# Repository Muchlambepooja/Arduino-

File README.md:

<!--Heading-->
# Arduino-Board
<!--links-->

##  Table of Contents

* [1. Introduction]()

* [2.Power Module](https://user-images.githubusercontent.com/91477166/134933617-c281e0b7-52b0-430e-a4fc-98a04329524c.PNG)

* [3. Voltage Regulator](https://user-images.githubusercontent.com/91477166/137732301-d14b79bf-847d-4a53-ac1d-5a26da9be1a0.jpg)

* [4. Power_jackpth_lock](https://user-images.githubusercontent.com/91477166/137733125-0d70d7f8-92f7-4a11-a70f-299146b748ae.png)

* [5. Capacitor](https://user-images.githubusercontent.com/91477166/137733573-614a9385-2981-4580-8750-bcf8b14b4d77.jpg)

* [6. Microcontroller](https://user-images.githubusercontent.com/91477166/134943802-9d5f9fb5-34e9-4055-a048-e4feaa09a2d5.PNG)

* [7. Schematic](https://user-images.githubusercontent.com/91477166/134953086-77eabae7-3045-4bdb-ab8c-5c033848843d.png)

* [8. Board](https://user-images.githubusercontent.com/91477166/134954367-aeb1af29-25dc-444c-b872-aa8de7bfb5b1.png)

* [9. Top Layer](https://user-images.githubusercontent.com/91477166/134954817-afc4833a-c6b3-4553-b30f-944d2f450a21.png)

* [10. Bottom Layer](https://user-images.githubusercontent.com/91477166/134955356-d5f6bea5-aa2f-4f7f-b24b-226915f9a1c8.png)

* [11. Future Scope]()

* [12. Contributors]()

<!---links-->

# Introduction :
This repository presents  the design of Arduino Board .The boards are equipped with sets of digital and analog input/output (I/O) pins that may be interfaced to various expansion boards ('shields') or breadboards (for prototyping) and other circuits. The boards feature serial communications interfaces, we need to use external  Universal Serial Bus (USB) on some models, which are also used for loading programs . 

The below figure shows the power module of arduino board using eagle tool.

# Power Module

This Power Module Consist of Voltage Regulator, Power_jackpth_lock, 2-Capacitors and vcc.with Input voltage 7V to 16V .

##  Voltage Regulator:
A voltage regulator is a system designed to automatically maintain a constant voltage. A voltage regulator may use a simple feed-forward design or may include negative feedback. It may use an electromechanical mechanism, or electronic components. Depending on the design, it may be used to regulate one or more AC or DC voltages.
Electronic voltage regulators are found in devices such as computer power supplies where they stabilize the DC voltages used by the processor and other elements. In automobile alternators and central power station generator plants, voltage regulators control the output of the plant. In an electric power distribution system, voltage regulators may be installed at a substation or along distribution lines so that all customers receive steady voltage independent of how much power is drawn from the line.

##  Power_jackpth_lock:
Power circuit wired up
Whenever a net splits in two directions a junction node is created. This signifies that all three intersecting nets are connected. If two nets cross, but there's not a junction, those nets are not connected.

##  Capacitor:
A capacitor is a device that stores electrical energy in an electric field. It is a passive electronic component with two terminals.
The effect of a capacitor is known as capacitance. While some capacitance exists between any two electrical conductors in proximity in a circuit, a capacitor is a component designed to add capacitance to a circuit. The capacitor was originally known as a condenser or condensator.This name and its cognates are still widely used in many languages, but rarely in English, one notable exception being condenser microphones, also called capacitor microphones.

##  Microcontroller:

ATmega328P is a high performance yet low power consumption 8-bit AVR microcontroller that’s able to achieve the most single clock cycle execution of 131 powerful instructions thanks to its advanced RISC architecture. It can commonly be found as a processor in Arduino boards such as Arduino Fio and Arduino Uno.

##  Features and Parametrics

### Features:
High endurance non-volatile memory segments

In system self-programmable flash program memory
Programming Lock for software security

###  Peripheral feature:

Two 8-bit Timer/Counter with separate prescaler, compare mode.
One 16-bit Timer/Counter with separate prescaler, compare mode, and capture mode

###   Temperature measurement:

Programmable serial USART and watchdog timer with separate on-chip oscillator

Unique features compared to other microcontrollers (ARM, 8051, PIC):

Power-on reset and programmable brown-out detection
Internal calibrated oscillator
External and Internal interrupt sources

Six sleep modes: Idle, ADC noise reduction, power-save, power-down, standby, and extended standby

###  Parametrics:

Program Memory Type:	Flash

Program Memory Size:	32

CPU Speed (MIPS/DMIPS) :	20

SRAM (KB)	:2,048

Data EEPROM/HEF (bytes)	1,024

Digital Communication Peripheral :	1-UART, 2-SPI, 1-I2C

Capture/Compare/PWM Peripheral :	1 Input Capture, 1 CCP, 6PWM

Number of Comparators :	1

Temperature Range	: -40 to 85deg

Operating Voltage Range (V) :	1.8 to 5.5V

Pin Count	: 28

Low Power:	Yes

###  Advantages and Disadvantages:

####  Advantages:

Processors are simpler to use, with the usage of 8bit and 16bit instead of 32/64bit which are more complex
Readily usable without additional computing components with 32k bytes of onboard self-programmable flash program memory as well as 23 programmable I/O lines
Code Efficient, all 31 registers are directly connected to the arithmetic logic unit (ALU), making it 10 times faster than conventional CISC microcontrollers
Optimized for AVR enhanced RISC instruction set.

#### Disadvantages:

Lacks performance compared to higher bit microcontrollers
Product Applications
The ATmega328P is supported with a full suite of program and system development tools which includes: C compilers, macro assemblers, program debugger/simulators, in-circuit emulators, and evaluation kits.

The fast PWM mode that provides a high-frequency PWM waveform generation allows for it to be suited for power regulation, rectification, and DAC applications.

We have also used Header Pins as shown below

# Schematic

The Arduino project began in 2005 as a tool for students at the Interaction Design Institute Ivrea, Italy, aiming to provide a low-cost and easy way for novices and professionals to create devices that interact with their environment using sensors and actuators. Common examples of such devices intended for beginner hobbyists include simple robots, thermostats and motion detectors.

##   Board:

##  Top layer:

##  Bottom Layer:

##  Future Scope:

the Arduino platform has done is to take what was once a fragmented and expensive market for robotics and microprocessors and become the major platform, largely by virtue of much lower cost and ease of use, leading to higher volume and popularity, and community support behind it. Arduino has made it simple to program their boards with any computer via USB and simple to integrate with a wide array of sensors and devices.

##  Contributors:

 Muchlambe Pooja ,B.Tech(Electronics and Communication Engineering), Jawaharlal Nehru Technological University, Hyderabad.

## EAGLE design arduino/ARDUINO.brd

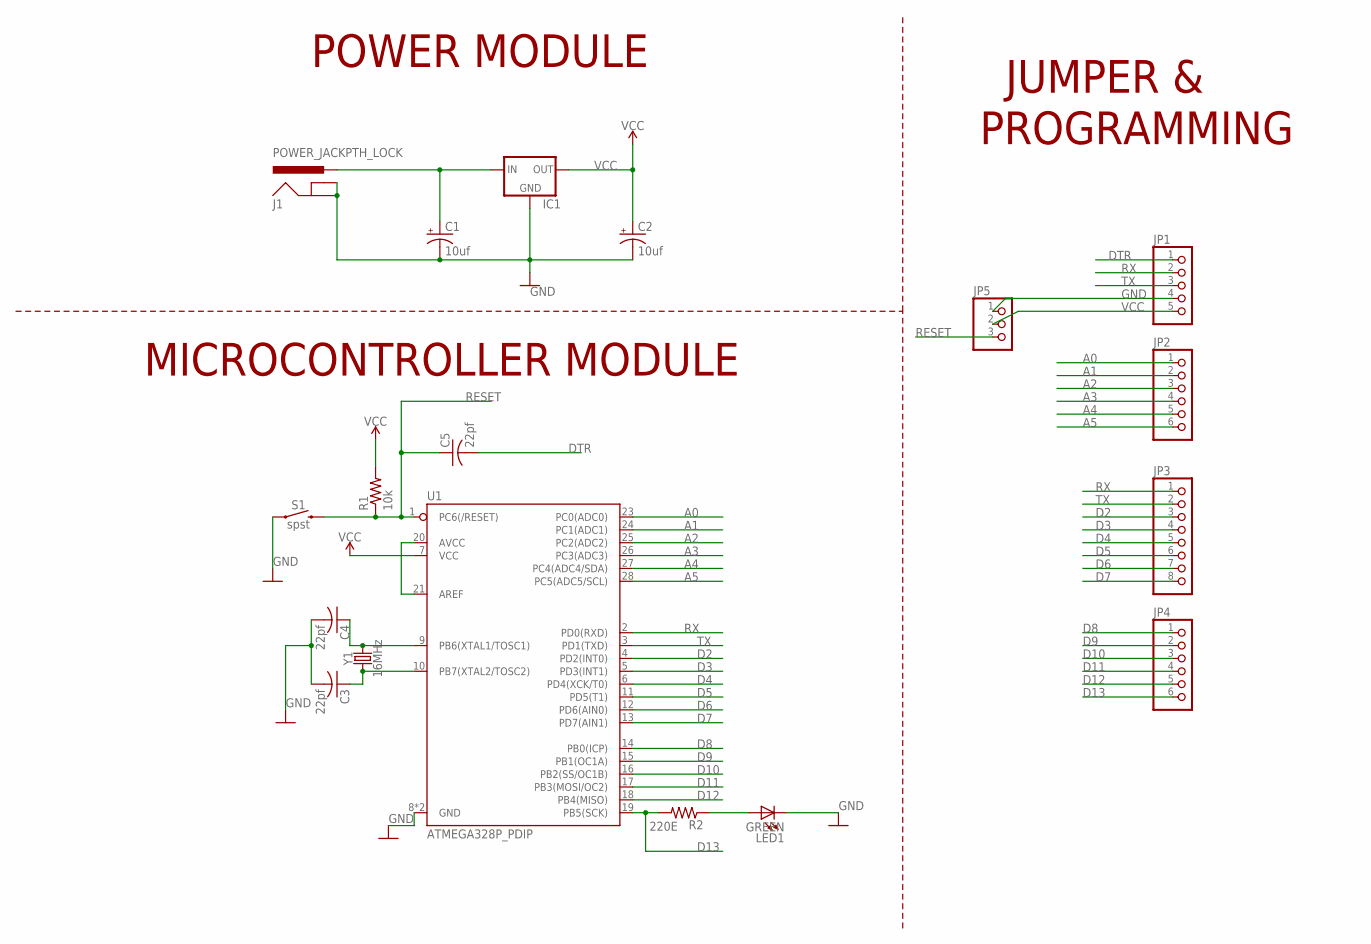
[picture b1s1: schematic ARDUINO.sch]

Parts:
C1, C2: 10uf; E2,5-6E
C3, C4, C5: 22pf; C025-024X044
IC1: MCP1700TRI; TO92
J1: POWER_JACKPTH_LOCK; POWER_JACK_PTH_LOCK
JP1: PINHD-1X5; 1X05
JP2, JP4: PINHD-1X6; 1X06
JP3: PINHD-1X8; 1X08
JP5: PINHD-1X3; 1X03
LED1: GREEN; LED3MM
R1: 10k; 0204/7
R2: 220E; 0204/7
S1: spst; TACTILE_SWITCH_PTH_6.0MM
U1: ATMEGA328P_PDIP; DIP28
Y1: 16MHz; HC49US

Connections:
A0: JP2.1, U1.23 (PC0(ADC0))
A1: JP2.2, U1.24 (PC1(ADC1))
A2: JP2.3, U1.25 (PC2(ADC2))
A3: JP2.4, U1.26 (PC3(ADC3))
A4: JP2.5, U1.27 (PC4(ADC4/SDA))
A5: JP2.6, U1.28 (PC5(ADC5/SCL))
D2: JP3.3, U1.4 (PD2(INT0))
D3: JP3.4, U1.5 (PD3(INT1))
D4: JP3.5, U1.6 (PD4(XCK/T0))
D5: JP3.6, U1.11 (PD5(T1))
D6: JP3.7, U1.12 (PD6(AIN0))
D7: JP3.8, U1.13 (PD7(AIN1))
D8: JP4.1, U1.14 (PB0(ICP))
D9: JP4.2, U1.15 (PB1(OC1A))
D10: JP4.3, U1.16 (PB2(SS/OC1B))
D11: JP4.4, U1.17 (PB3(MOSI/OC2))
D12: JP4.5, U1.18 (PB4(MISO))
D13: JP4.6, R2.2, U1.19 (PB5(SCK))
DTR: C5.2, JP1.1
GND: C1.-, C2.-, C3.2, C4.2, IC1.1 (GND), J1.GND, J1.GNDBREAK, JP1.4, JP5.1, LED1.K (C), S1.1, U1.8 (GND), U1.22 (GND)
unnamed: C1.+, IC1.2 (IN), J1.PWR
unnamed: C4.1, U1.9 (PB6(XTAL1/TOSC1)), Y1.2
unnamed: C3.1, U1.10 (PB7(XTAL2/TOSC2)), Y1.1
unnamed: U1.20 (AVCC), U1.21 (AREF)
unnamed: LED1.A, R2.1
RESET: C5.1, JP5.3, R1.1, S1.3 (2), U1.1 (PC6(/RESET))
RX: JP1.2, JP3.1, U1.2 (PD0(RXD))
TX: JP1.3, JP3.2, U1.3 (PD1(TXD))
VCC: C2.+, IC1.3 (OUT), JP1.5, JP5.2, R1.2, U1.7 (VCC)

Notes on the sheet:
POWER MODULE
JUMPER &
PROGRAMMING
MICROCONTROLLER MODULE

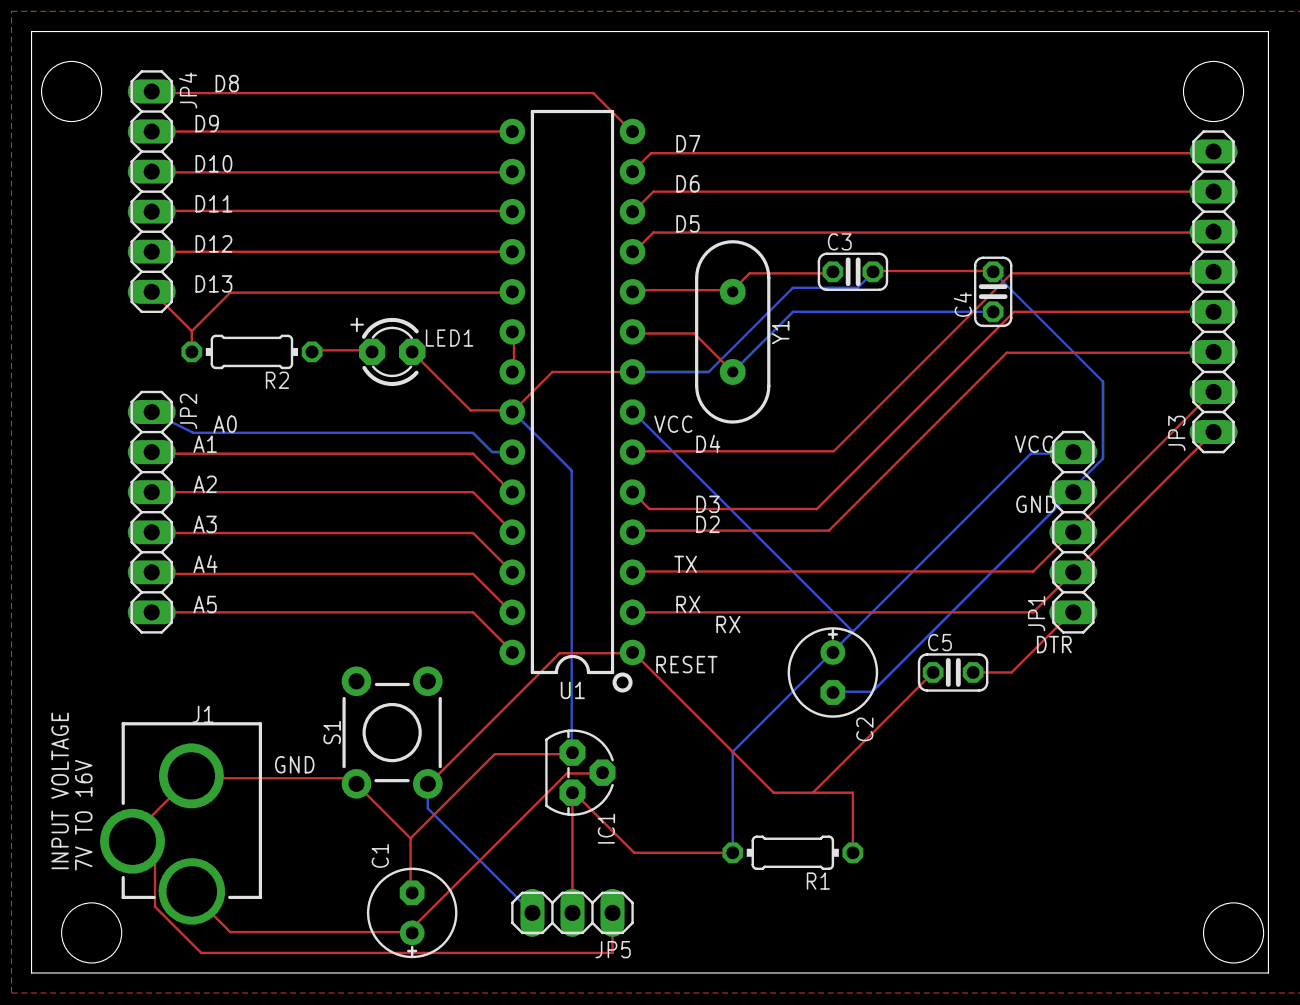
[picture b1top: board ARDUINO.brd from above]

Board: 2 copper layers, 78.4 x 59.7 mm, 18 parts (0 on the bottom side), 29 nets.

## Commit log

2021-09-27 Create Introduction
2021-10-18 LICENSE

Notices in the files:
parts and their libraries:
SparkFun-Connectors: Licensing: Creative Commons ShareAlike 4.0 International - https://creativecommons.org/licenses/by-sa/4.0
